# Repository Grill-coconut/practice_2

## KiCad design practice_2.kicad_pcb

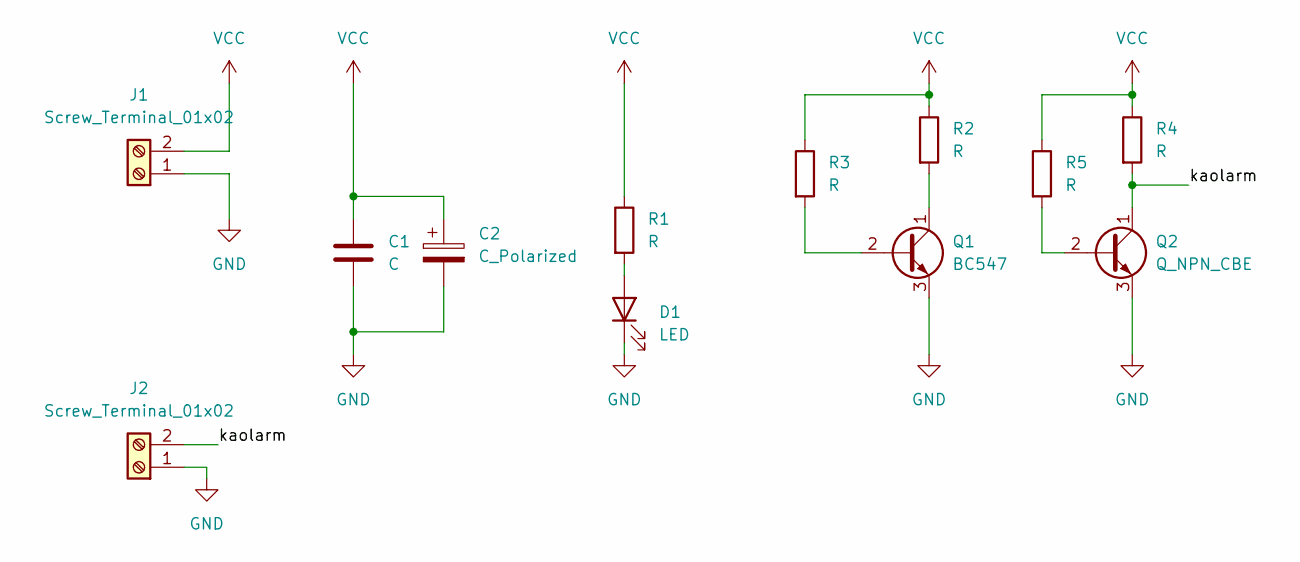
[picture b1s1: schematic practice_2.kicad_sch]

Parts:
C1: C; C_Radial_D10.0mm_H12.5mm_P5.00mm
C2: C_Polarized; CP_Radial_D10.0mm_P5.00mm
D1: LED; LED_D3.0mm
J1, J2: Screw_Terminal_01x02; TerminalBlock_MaiXu_MX126-5.0-02P_1x02_P5.00mm
Q1: BC547; TO-92_Inline
Q2: Q_NPN_CBE; TO-92L_Inline_Wide
R1, R2, R3, R4, R5: R; R_Axial_DIN0309_L9.0mm_D3.2mm_P12.70mm_Horizontal

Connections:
/kaolarm: J2.2, Q2.1 (C), R4.2
GND: C1.2, C2.2, D1.1 (K), J1.1, J2.1, Q1.3 (E), Q2.3 (E)
unnamed: D1.2 (A), R1.2
unnamed: Q1.2 (B), R3.2
unnamed: Q1.1 (C), R2.2
unnamed: Q2.2 (B), R5.2
VCC: C1.1, C2.1, J1.2, R1.1, R2.1, R3.1, R4.1, R5.1

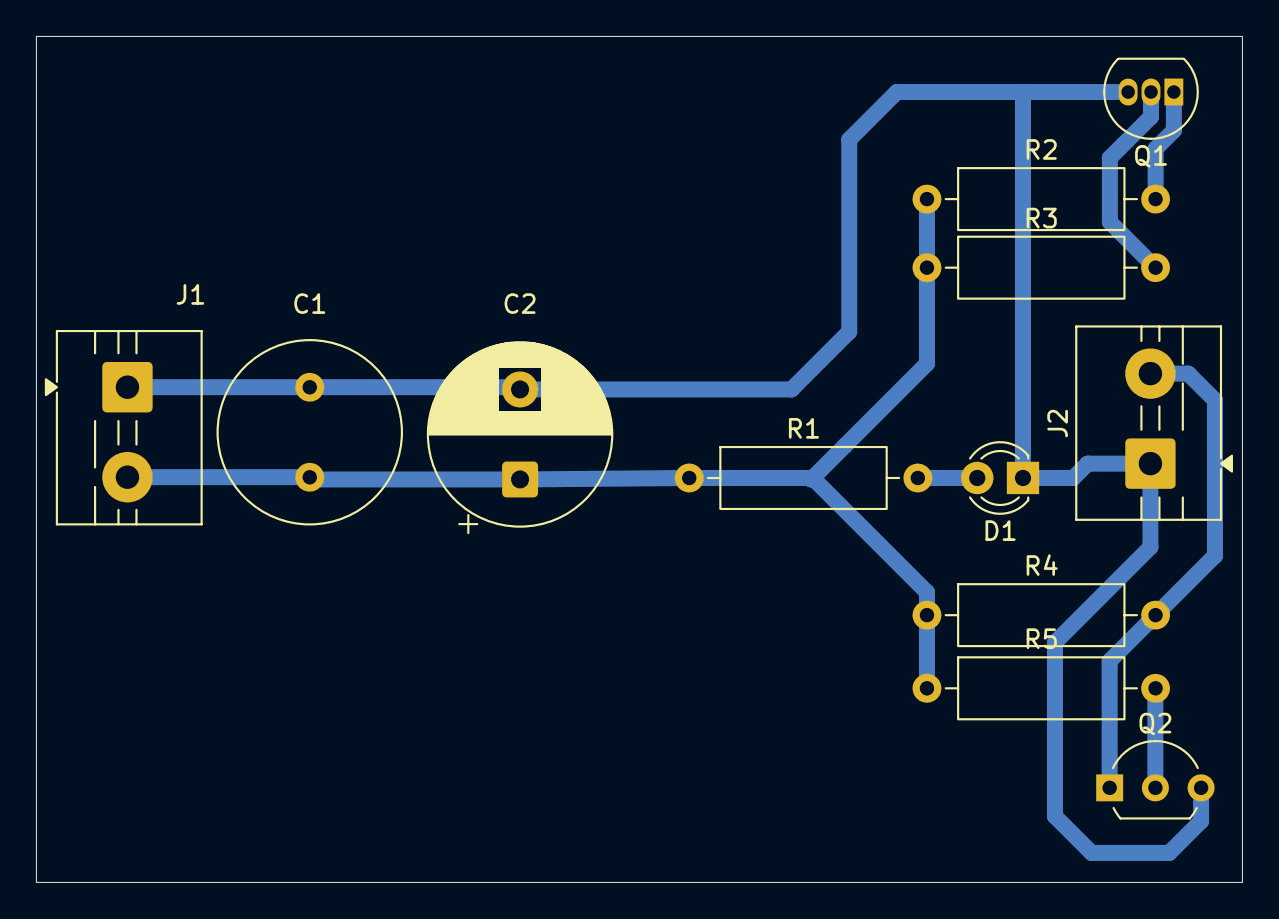
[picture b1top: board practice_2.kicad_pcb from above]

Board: 2 copper layers, 67.0 x 47.0 mm, 12 parts (0 on the bottom side), 7 nets.
